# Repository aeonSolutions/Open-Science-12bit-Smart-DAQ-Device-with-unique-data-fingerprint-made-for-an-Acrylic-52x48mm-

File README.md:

<br>

[PCB-Prototyping-Catalogue](https://github.com/aeonSolutions/PCB-Prototyping-Catalogue)  >>  [Open Scientific Research](https://github.com/aeonSolutions/Open-Scientific-Research)  >>  12bit-Smart-DAQ-unique-data-fingerprint-made-for-an-Acrylic-52x48mm

# 12bit Smart DAQ Device with unique data fingerprint and a 1.69" TFT LCD made for an Acrylic 52x48mm  Enclosure

This is the repository for the 12bit Smart DAQ Device with unique data fingerprint able to do experimental data upload to any data repository. For detailed information head to the main project Wiki [here](https://github.com/aeonSolutions/openScience-Smart-DAQ-to-Upload-Live-Experimental-Data-to-a-Data-Repository/wiki). Thank you.

<br>

### 12bit Smart DAQ  Hardware Specifications
The hardware specifications for the 12bit PCB with dimensions of 52x46mm are the following:

- QFN 56 Dual Xtensa LX7 Core Processors running up to 240MHz
  -	RISC V ultra-low power co-processor
  - 512Kb RAM (PSRAM max 1 Gb);
  - 16Mb SOIC 8 NOR SPI Flash Memory (max 1Gb);
  - 2.4GHz ISM wireless connectivity;
  - Up to 118 12bit ADC Multiplexed DAQ channels;

<br>

- Onboard Storage:
  - 2x SPI Flash WSON-8 Chips for local storage upwards of 4Gbytes. 

<br>

- Authentication & Security:
  - SOIC-8 ATSHA204A SHA-256 high-security hardware authentication IC for secure and unique experimental data exchange

<br>

- Power management
  - DFN-6 AUR9718/ST1S09 high efficiency step-down 3.3V 1.5A DC converter;
  - CN3065 4.2V Lipo Battery Management System
  - USB-C connection for 5.0V 1.0A power supply from any power charger found on smartphones or tablets.
  - JST SH 2 pin 1.0mm for specific power supply applications (3.3V to 5.0V 1.0A DC)    

<br>

- Connectivity
  - 2.4GHz WIFI
  - Bluetooth & BLE
  - USB-C serial communication
  - JTAG debugger connector
  - Serial UART connector
  
<br>

- Onboard sensors:
  - DFN-8 AHT20; temperature sensor with a precision of 0.1 C;
  - DFN-8 AHT20 humidity sensor;
  - LGA-14 LSM6DS3 a 6-axis accelerometer and gyroscope;
  - TEMT6000 Luminosity Sensor;
  - SOT 23-3 reference voltage sensor;

<br>

- External connectivity for up to 118 sensors 12 to 16bit with onboard voltage reference analyzer with temperature compensation and automatic ADC calibration:
  -  1x I2C pin terminal connector (4 pin)
  -  1x ADC 12 to 16bit (with oversampling & digitization) digital terminal connector (3 pin)
  -  1x ADC Ohmmeter connection with 12 to 16bit (with oversampling & digitization) with manual scale selection via dip switch
 
<br>

- Display
  - 1.69" TFT LCD Display with a resolution of 320x280 px 

<br>

- Enclosure

This particular smart DAQ was designed to fit a well-known ABS enclosure commercially available on the internet. For instance [here](https://s.click.aliexpress.com/e/_DCKIAm1) on AliExpress. 

<br>

<br>

<p align="center">

</p>

<br>

###  Status

Fully tested and working

 **Known PCB bugs [April 04-2023 pcb revision] :**
 
UART SH connector GND pin requires connection to GND on the PCB (easy fix. as it is exactly next to the GND pin). This only affects the onboard firmware upload UART port (the OEM firmware available here is able to do OTA updates using WIFI) .   

<br>

<p align="center">     

</p>

<br>

## What one additionally needs
- [USB to UART/USB TTL firmware burner for 5V and 3.3V MCUs ](https://github.com/aeonSolutions/PCB-Prototyping-Catalogue/blob/main/DIY-Maker/README.md) 

<br />
<br />

## Dataverse API C library

In paralell is being written a C library to expedite API integration on smart DAQ devices or elsewhere. Follow the link to its repository:

https://github.com/aeonSolutions/OpenScience-Dataverse-API-C-library

<p align="center">
  
</p>

<br>

**Dataverse API in another coding language**

Goto dataverse.org for another coding language that best suits your coding style and needs. Currently there are client libraries for Python, Javascript, R, Java, and Julia that can be used to develop against Dataverse Software APIs

https://guides.dataverse.org/en/5.12/api/client-libraries.html

<br>
<br>

-----------------------------------------------------------------------------------

**Get a Notification on every PCB update**

|  | You can fill in your [email here (Google form)](https://docs.google.com/forms/d/e/1FAIpQLScErMgQYRdA-umvCjvTPPrCO7Lg1QYowTxb7vfa8cTfrcPEAA/viewform?usp=pp_url) and I'll send a reminder when a new PCB prototype is made available here or a new revision for an existing PCB. Stay tuned! |
|-------------|------|

<br />

**Be supportive of my dedication and work towards open hardware and buy me a cup of coffee. Links below. Above and on the side**

<br />
<br />

## Q&A WhatsApp/Telegram Groups
|  | Subscribe to the WhatsApp or Telegram channel to get latest information about any of this KiCad projects and get help. Or simply like this kind of projects and want to stay updated with the latest research ideas and prototypes during the day and week.   |
|-------------|------|

<br />
<br />

## Usefull Utilities 
|  | One can find here usefull utilities to use when designing and prototyping pcb electronics. For instance a simple excel spreadsheet with resistance divider finder compatible with all sold on [aliexpress](https://www.aliexpress.com/item/1005002792418456.html?spm=a2g0o.cart.0.0.22e538dayDM1YR&mp=1). Click on the Excel logo to the left to get them! |
|-------------|------|

<br />
<br />

## Author

You can get in touch with me on my LinkedIn Profile:

*Miguel Tomas* : 

You can also follow my GitHub Profile to stay updated about my latest projects: 

<br>

### Be supportive of my dedication and work towards open innovation & technology solutions and buy me a cup of coffee
The PCB Design Files I provide here for anyone to use are free. If you like this Smart Device or use it, please consider buying me a cup of coffee, a slice of pizza, or a book to help me study, eat and think new PCB design files.

<p align+"left">

<br>

</p>

<br />

### Make a donation on Paypal
Make a donation on PayPal and get a TAX refund*.

<br>

### Support all these open hardware projects and become a Patreon  
Liked any of my PCB KiCad Designs? Help and Support my open work to all by becoming an LDAD Patreon.
In return, I will give a free PCB design in KiCad to all Patreon supporters. To learn more go to patreon.com. Link below.

<br />
<br />

______________________________________________________________________________________________________________________________
### License
2023 Creative Commons Attribution-NonCommercial-ShareAlike 4.0 International

https://creativecommons.org/licenses/by-nc-sa/4.0/

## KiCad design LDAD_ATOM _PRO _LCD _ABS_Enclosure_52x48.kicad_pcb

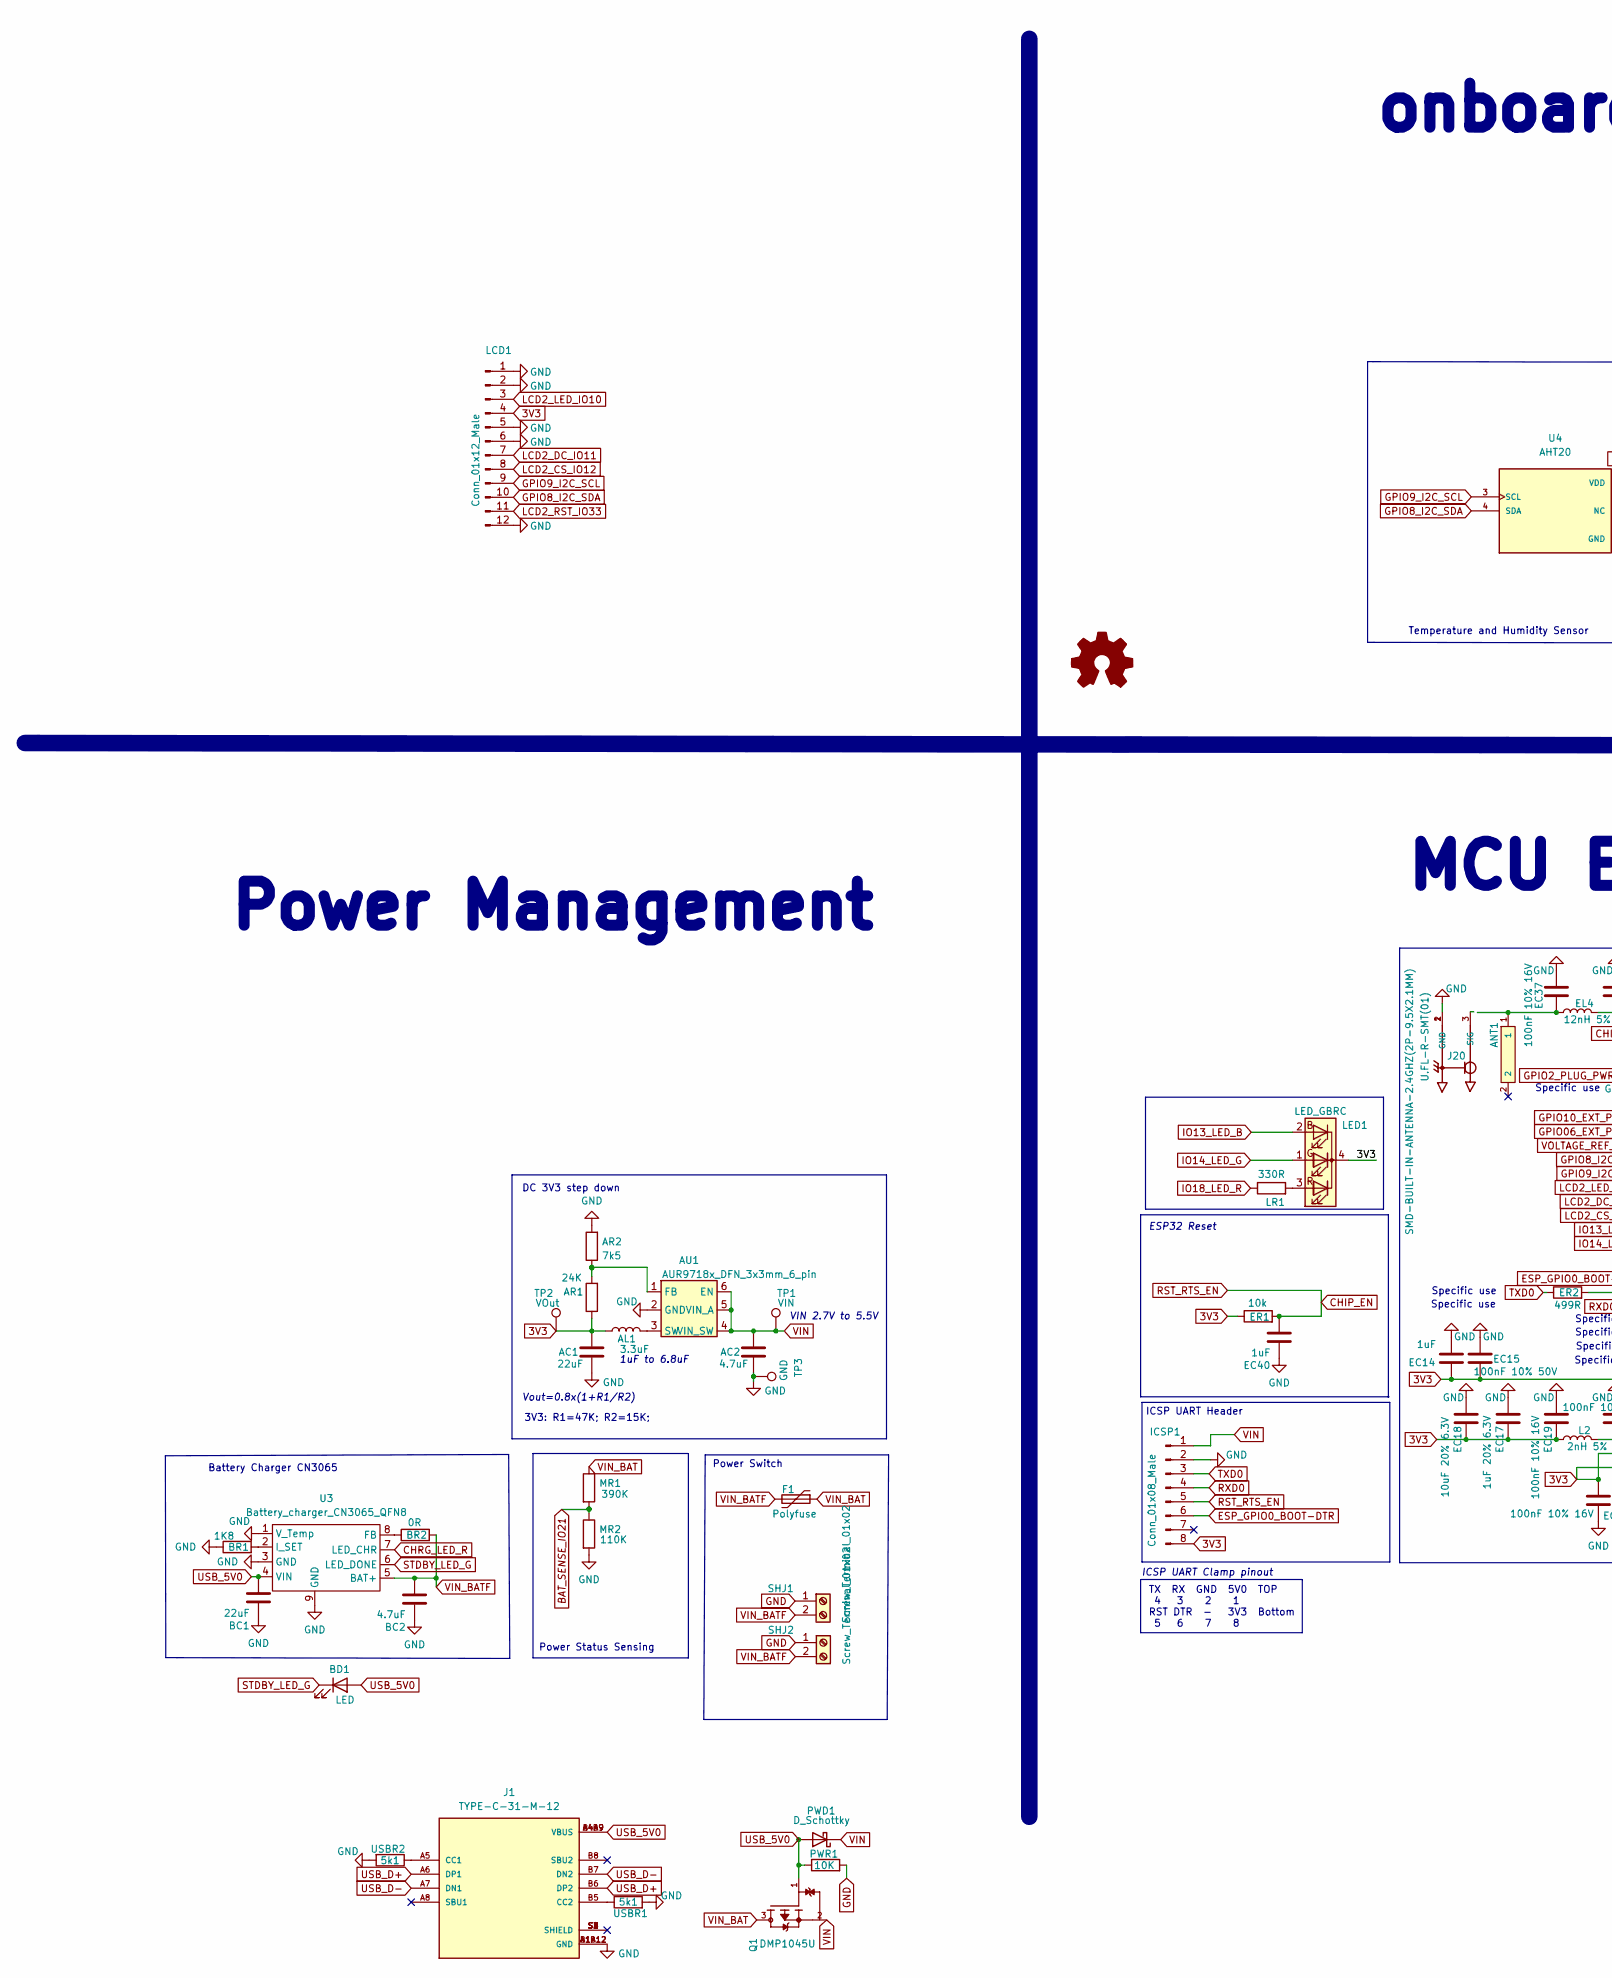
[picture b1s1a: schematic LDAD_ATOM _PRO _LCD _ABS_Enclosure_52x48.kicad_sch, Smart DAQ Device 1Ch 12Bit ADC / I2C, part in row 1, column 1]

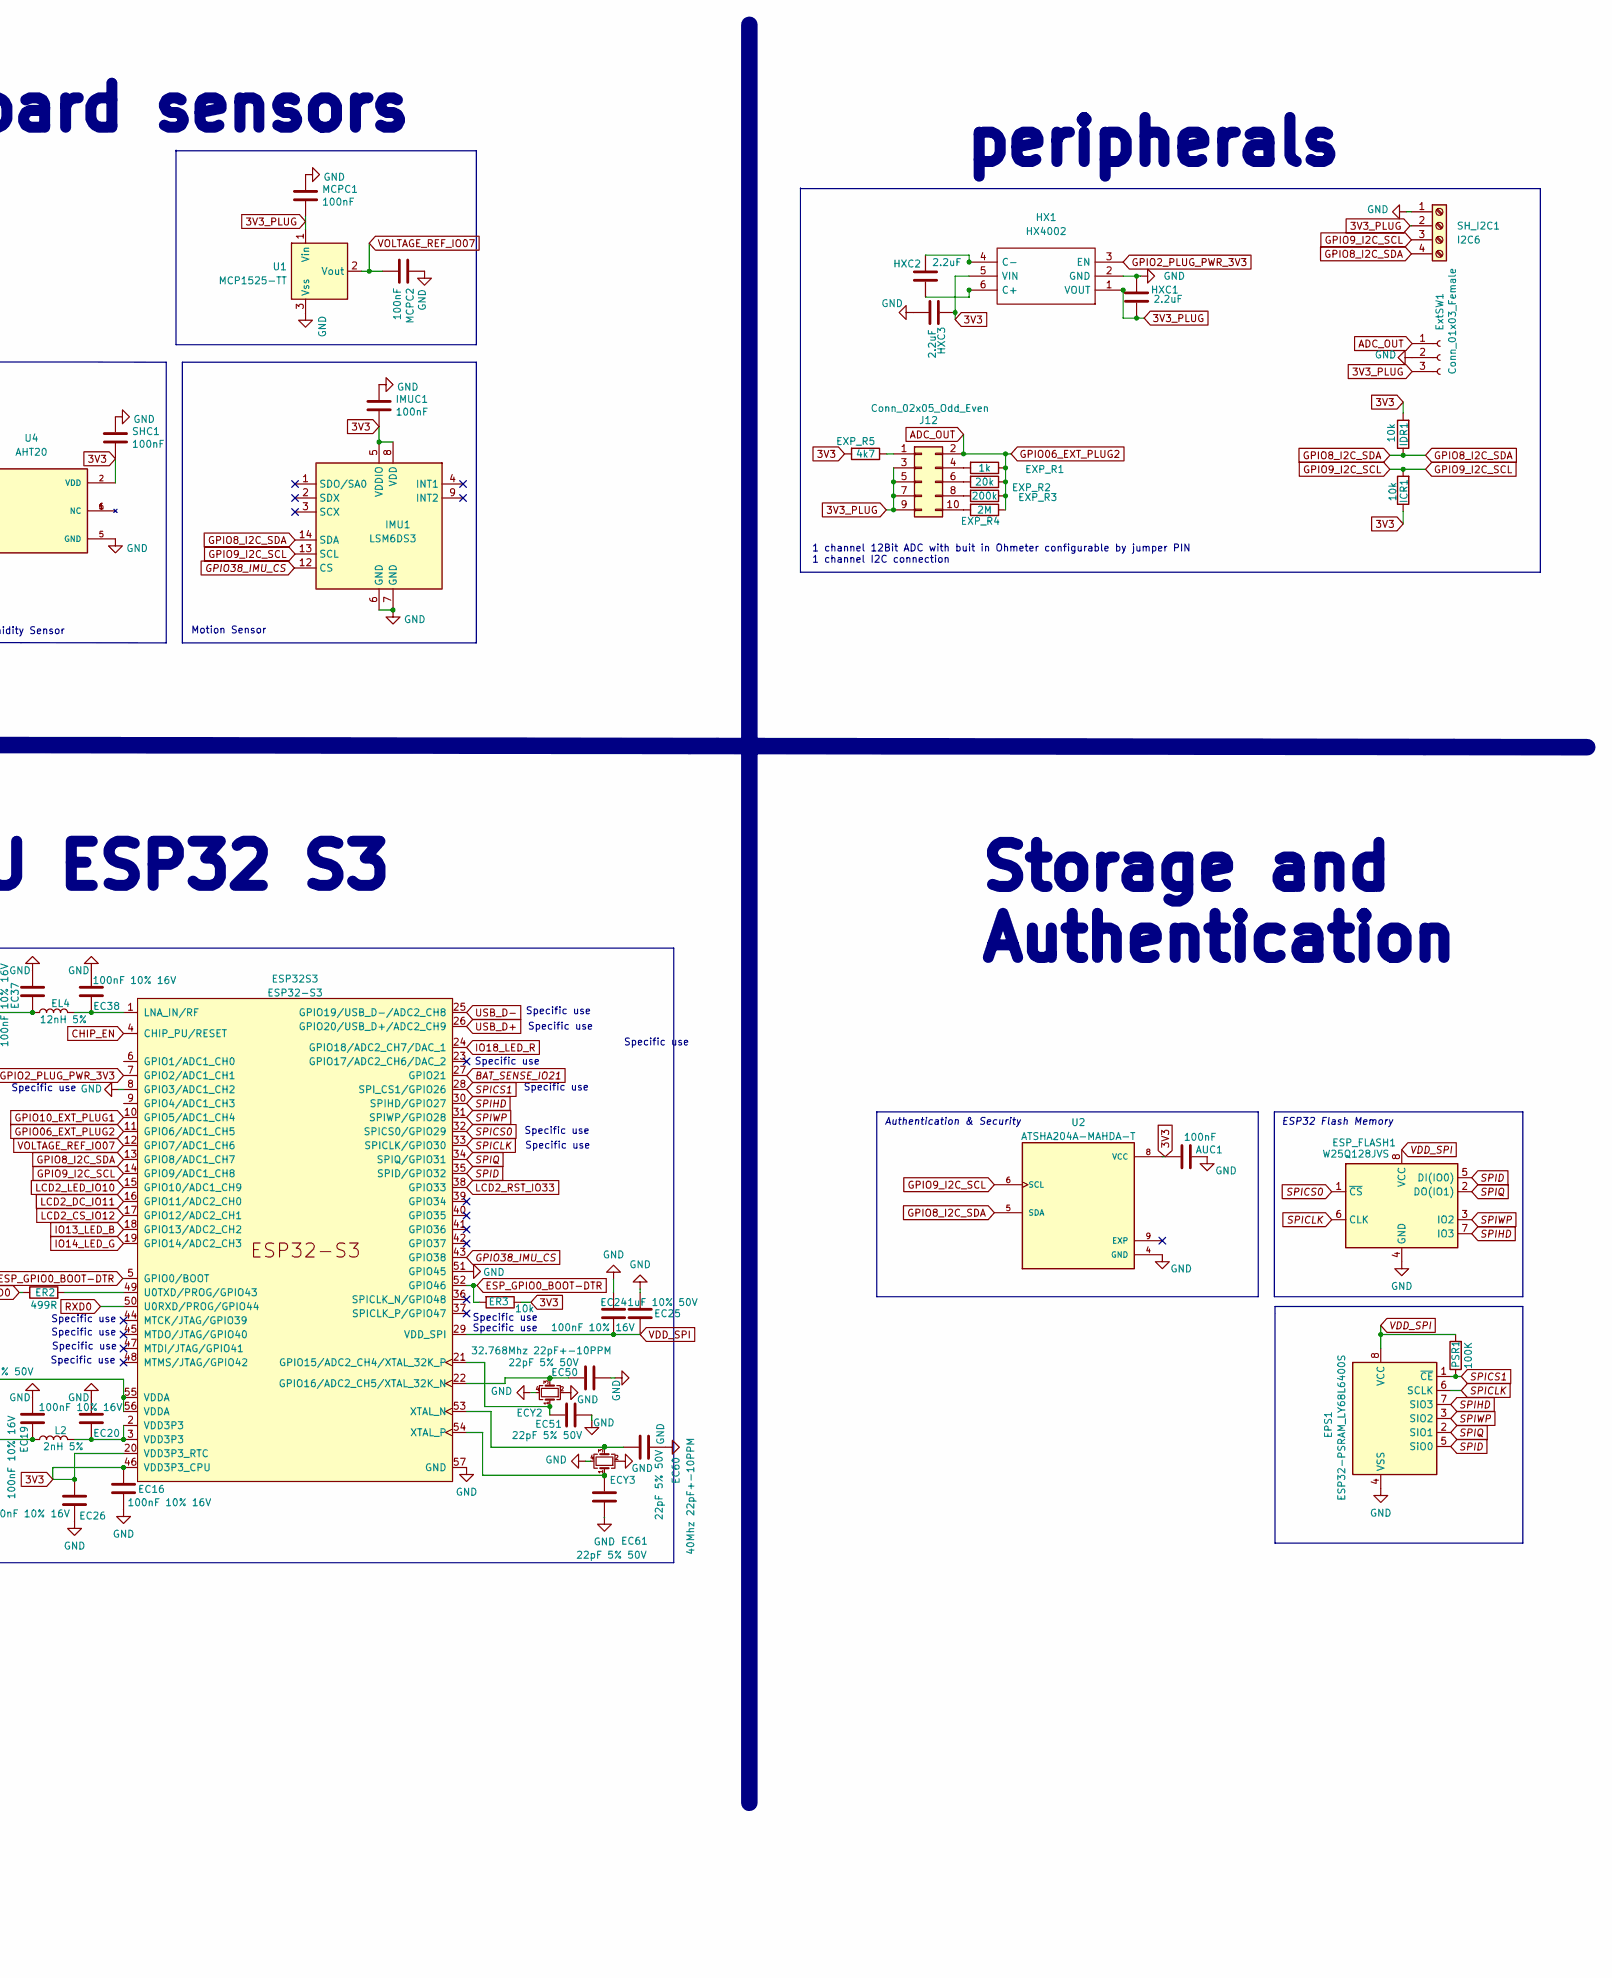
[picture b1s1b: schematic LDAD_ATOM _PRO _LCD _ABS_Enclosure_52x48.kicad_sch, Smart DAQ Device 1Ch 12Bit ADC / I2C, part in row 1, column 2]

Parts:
AC1: 22uF; C_0805_2012Metric_Pad1.18x1.45mm_HandSolder
AC2: 4.7uF; C_0805_2012Metric_Pad1.18x1.45mm_HandSolder
AL1: 3.3uF; L_1210_3225Metric
ANT1: SMD-BUILT-IN-ANTENNA-2.4GHZ(2P-9.5X2.1MM); AN9520_ANT2-SMD-9.5X2.1X1.0MM
AR1: 24K; R_0805_2012Metric_Pad1.20x1.40mm_HandSolder
AR2: 7k5; R_0805_2012Metric_Pad1.20x1.40mm_HandSolder
AU1: AUR9718x_DFN_3x3mm_6_pin; AUR9718 3x3mm 6 pin
AUC1: 100nF; C_0603_1608Metric
BC1: 22uF; C_0805_2012Metric
BC2: 4.7uF; C_0805_2012Metric
BD1: LED; LED_0805_2012Metric
BR1: 1K8; R_0603_1608Metric
BR2: 0R; R_0603_1608Metric
EC14: 1uF; C_0805_2012Metric
EC15: 100nF 10% 50V; C_0603_1608Metric
EC16, EC19, EC20, EC24, EC26, EC37, EC38: 100nF 10% 16V; C_0603_1608Metric
EC17: 1uF 20% 6.3V; C_0603_1608Metric
EC18: 10uF 20% 6.3V; C_0805_2012Metric
EC25: 1uF 10% 50V; C_0603_1608Metric
EC40: 1uF; C_0603_1608Metric
EC50, EC51, EC60, EC61: 22pF 5% 50V; C_0603_1608Metric
ECY2: 32.768Mhz 22pF+-10PPM; Crystal_SMD_EuroQuartz_MT-4Pin_3.2x2.5mm
ECY3: 40Mhz 22pF+-10PPM; Crystal_SMD_EuroQuartz_MT-4Pin_3.2x2.5mm
EL4: 12nH 5%; L_0805_2012Metric
EPS1: ESP32-PSRAM_LY68L6400S; SOIC-8_3.9x4.9mm_P1.27mm
ER1, ER3: 10k; R_0603_1608Metric
ER2: 499R; R_0603_1608Metric
ESP32S3: ESP32-S3; QFN-56-1EP_7x7mm_P0.4mm_EP5.6x5.6mm
ESP_FLASH1: W25Q128JVS; Flash SPI SON127P800X600X80-9N
EXP_R1: 1k; R_0603_1608Metric
EXP_R2: 20k; R_0603_1608Metric
EXP_R3: 200k; R_0603_1608Metric
EXP_R4: 2M; R_0603_1608Metric
EXP_R5: 4k7; R_0603_1608Metric
ExtSW1: Conn_01x03_Female; JST_SH_SM03B-SRSS-TB_1x03-1MP_P1.00mm_Horizontal
F1: Polyfuse; Fuse_1206_3216Metric_Pad1.42x1.75mm_HandSolder
HX1: HX4002; HX4002 SOT95 P280X125-6N; Manufacturer_Part_Number HX4002
HXC1, HXC2, HXC3: 2.2uF; C_0603_1608Metric
ICR1: 10k; R_0603_1608Metric
ICSP1: Conn_01x08_Male; SOIC_clipProgSmall
IDR1: 10k; R_0603_1608Metric
IMU1: LSM6DS3; LSM6DS3 PQFN50P300X250X86-14N
IMUC1: 100nF; C_0603_1608Metric
J1: TYPE-C-31-M-12; USB C HRO_TYPE-C-31-M-12; PARTREV A
J12: Conn_02x05_Odd_Even; Dip Switch 5 pin 1.27mm SW_DS05-127-2-06BK-SMT-TR
J20: U.FL-R-SMT(01); HRS_U.FL-R-SMT(01)
L2: 2nH 5%; L_0805_2012Metric
LCD1: Conn_01x12_Male; 1.69 LCD TFT IPS 12pin
LED1: LED_GBRC; LED_1206_3210_RGB_Metric
LR1: 330R; R_0603_1608Metric
MCPC1, MCPC2: 100nF; C_0603_1608Metric
MR1: 390K; R_0805_2012Metric
MR2: 110K; R_0805_2012Metric
PSR1: 100K; R_0603_1608Metric
PWD1: D_Schottky; D_1206_3216Metric
PWR1: 10K; R_0805_2012Metric
Q1: DMP1045U; SOT-23; PARTREV 7 - 2
SHC1: 100nF; C_0603_1608Metric
SHJ1, SHJ2: Screw_Terminal_01x02; JST_SH_SM02B-SRSS-TB_1x02-1MP_P1.00mm_Horizontal
SH_I2C1: I2C6; JST_SH_SM04B-SRSS-TB_1x04-1MP_P1.00mm_Horizontal
TP1: VIN; TestPoint_Pad_D1.0mm
TP2: VOut; TestPoint_Pad_D1.0mm
TP3: GND; TestPoint_Pad_D1.0mm
U1: MCP1525-TT; SOT-23
U2: ATSHA204A-MAHDA-T; ATSHA204A Auth SOIC8; PART_REV A
U3: Battery_charger_CN3065_QFN8; QFN8 3.1x2.9mm QFNn-8 3x3 SON80P400X400X100-9N
U4: AHT20; AHT20 - PSON100P300X300X110-6N; PARTREV V1.0
USBR1, USBR2: 5k1; R_0603_1608Metric

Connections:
3V3: AC1.1, AL1.1, AR1.1, AUC1.2, EC14.2, EC15.2, EC16.1, EC17.1, EC18.1, EC19.1, EC26.1, ER1.1, ER3.1, ESP32S3.20 (VDD3P3_RTC), ESP32S3.46 (VDD3P3_CPU), ESP32S3.55 (VDDA), ESP32S3.56 (VDDA), EXP_R5.2, HX1.5 (VIN), HXC3.2, ICR1.1, ICSP1.8, IDR1.2, IMU1.5 (VDDIO), IMU1.8 (VDD), IMUC1.2, L2.1, LCD1.4, LED1.4 (K), SHC1.2, TP2.1, U2.8 (VCC), U4.2 (VDD)
3V3_PLUG: ExtSW1.3, HX1.1 (VOUT), HXC1.1, J12.3, J12.5, J12.7, J12.9, MCPC1.2, SH_I2C1.2, U1.1 (Vin)
ADC_OUT: ESP32S3.11 (GPIO6/ADC1_CH5), EXP_R1.1, EXP_R2.1, EXP_R3.1, EXP_R4.1, ExtSW1.1, J12.2
BAT_SENSE_IO21: ESP32S3.27 (GPIO21), MR1.2, MR2.1
CHIP_EN: EC40.2, ER1.2, ESP32S3.4 (CHIP_PU/RESET), ICSP1.5
CHRG_LED_R: U3.7 (LED_CHR)
ESP_GPIO0_BOOT-DTR: ER3.2, ESP32S3.5 (GPIO0/BOOT), ESP32S3.52 (GPIO46), ICSP1.6
GND: AC1.2, AC2.2, AR2.2, AU1.2 (GND), AUC1.1, BC1.1, BC2.1, BR1.1, EC14.1, EC15.1, EC16.2, EC17.2, EC18.2, EC19.2, EC20.2, EC24.2, EC25.2, EC26.2, EC37.2, EC38.2, EC40.1, EC50.2, EC51.2, EC60.2, EC61.2, ECY2.2, ECY2.4, ECY3.2, ECY3.4, EPS1.4 (VSS), ESP32S3.8 (GPIO3/ADC1_CH2), ESP32S3.51 (GPIO45), ESP32S3.57 (GND), ESP_FLASH1.4 (GND), ExtSW1.2, HX1.2 (GND), HXC1.2, HXC3.1, ICSP1.2, IMU1.6 (GND), IMU1.7 (GND), IMUC1.1, J1.A1B12 (GND), J1.B1A12 (GND), J20.1 (GND), J20.2 (GND), LCD1.1, LCD1.2, LCD1.5, LCD1.6, LCD1.12, MCPC1.1, MCPC2.1, MR2.2, PWR1.2, SHC1.1, SHJ1.1, SHJ2.1, SH_I2C1.1, TP3.1, U1.3 (Vss), U2.4 (GND), U3.1 (V_Temp), U3.3 (GND), U3.9 (GND), U4.5 (GND), USBR1.2, USBR2.2
GPIO2_PLUG_PWR_3V3: ESP32S3.7 (GPIO2/ADC1_CH1), HX1.3 (EN)
GPIO8_I2C_SDA: ESP32S3.13 (GPIO8/ADC1_CH7), IDR1.1, IMU1.14 (SDA), LCD1.10, SH_I2C1.4, U2.5 (SDA), U4.4 (SDA)
GPIO9_I2C_SCL: ESP32S3.14 (GPIO9/ADC1_CH8), ICR1.2, IMU1.13 (SCL), LCD1.9, SH_I2C1.3, U2.6 (SCL), U4.3 (SCL)
GPIO10_EXT_PLUG1: ESP32S3.10 (GPIO5/ADC1_CH4)
GPIO38_IMU_CS: ESP32S3.43 (GPIO38), IMU1.12 (CS)
IO13_LED_B: ESP32S3.18 (GPIO13/ADC2_CH2), LED1.2 (BA)
IO14_LED_G: ESP32S3.19 (GPIO14/ADC2_CH3), LED1.1 (GA)
IO18_LED_R: ESP32S3.24 (GPIO18/ADC2_CH7/DAC_1), LR1.1
LCD2_CS_IO12: ESP32S3.17 (GPIO12/ADC2_CH1), LCD1.8
LCD2_DC_IO11: ESP32S3.16 (GPIO11/ADC2_CH0), LCD1.7
LCD2_LED_IO10: ESP32S3.15 (GPIO10/ADC1_CH9), LCD1.3
LCD2_RST_IO33: ESP32S3.38 (GPIO33), LCD1.11
unnamed: AL1.2, AU1.3 (SW)
unnamed: ANT1.1, EC37.1, EL4.1
unnamed: AR1.2, AR2.1, AU1.1 (FB)
unnamed: BR1.2, U3.2 (I_SET)
unnamed: BR2.1, U3.8 (FB)
unnamed: EC20.1, ESP32S3.2 (VDD3P3), ESP32S3.3 (VDD3P3), L2.2
unnamed: EC38.1, EL4.2, ESP32S3.1 (LNA_IN/RF)
unnamed: EC50.1, ECY2.3, ESP32S3.22 (GPIO16/ADC2_CH5/XTAL_32K_N)
unnamed: EC51.1, ECY2.1, ESP32S3.21 (GPIO15/ADC2_CH4/XTAL_32K_P)
unnamed: EC60.1, ECY3.3, ESP32S3.53 (XTAL_N)
unnamed: EC61.1, ECY3.1, ESP32S3.54 (XTAL_P)
unnamed: ER2.2, ESP32S3.49 (U0TXD/PROG/GPIO43)
unnamed: EXP_R1.2, J12.4
unnamed: EXP_R2.2, J12.6
unnamed: EXP_R3.2, J12.8
unnamed: EXP_R4.2, J12.10
unnamed: EXP_R5.1, J12.1
unnamed: HX1.4 (C-), HXC2.2
unnamed: HX1.6 (C+), HXC2.1
unnamed: J1.A5 (CC1), USBR2.1
unnamed: J1.B5 (CC2), USBR1.1
unnamed: LED1.3 (RA), LR1.2
RXD0: ESP32S3.50 (U0RXD/PROG/GPIO44), ICSP1.4
SPICLK: EPS1.6 (SCLK), ESP32S3.33 (SPICLK/GPIO30), ESP_FLASH1.6 (CLK)
SPICS0: ESP32S3.32 (SPICS0/GPIO29), ESP_FLASH1.1 (~CS)
SPICS1: EPS1.1 (~CE), ESP32S3.28 (SPI_CS1/GPIO26), PSR1.1
SPID: EPS1.5 (SiO0), ESP32S3.35 (SPID/GPIO32), ESP_FLASH1.5 (DI(IO0))
SPIHD: EPS1.7 (SIO3), ESP32S3.30 (SPIHD/GPIO27), ESP_FLASH1.7 (IO3)
SPIQ: EPS1.2 (SIO1), ESP32S3.34 (SPIQ/GPIO31), ESP_FLASH1.2 (DO(IO1))
SPIWP: EPS1.3 (SIO2), ESP32S3.31 (SPIWP/GPIO28), ESP_FLASH1.3 (IO2)
STDBY_LED_G: BD1.1 (K), U3.6 (LED_DONE)
TXD0: ER2.1, ICSP1.3
USB_5V0: BC1.2, BD1.2 (A), J1.A4B9 (VBUS), J1.B4A9 (VBUS), PWD1.2 (A), PWR1.1, Q1.1, U3.4 (VIN)
USB_D+: ESP32S3.26 (GPIO20/USB_D+/ADC2_CH9), J1.A6 (DP1), J1.B6 (DP2)
USB_D-: ESP32S3.25 (GPIO19/USB_D-/ADC2_CH8), J1.A7 (DN1), J1.B7 (DN2)
VDD_SPI: EC24.1, EC25.1, EPS1.8 (VCC), ESP32S3.29 (VDD_SPI), ESP_FLASH1.8 (VCC), PSR1.2
VIN: AC2.1, AU1.4 (VIN_SW), AU1.5 (VIN_A), AU1.6 (EN), ICSP1.1, PWD1.1 (K), Q1.2, TP1.1
VIN_BAT: F1.1, MR1.1, Q1.3
VIN_BATF: BC2.2, BR2.2, F1.2, SHJ1.2, SHJ2.2, U3.5 (BAT+)
VOLTAGE_REF_IO07: ESP32S3.12 (GPIO7/ADC1_CH6), MCPC2.2, U1.2 (Vout)

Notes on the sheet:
Specific use
3V3: R1=47K; R2=15K;
ICSP UART Header
peripherals
Vout=0.8x(1+R1/R2)
ESP32 Flash Memory
DC 3V3 step down
ESP32 Reset
Temperature and Humidity Sensor
1uF to 6.8uF
Motion Sensor
1 channel 12Bit ADC with buit in Ohmeter configurable by jumper PIN 1 channel I2C connection
onboard sensors
ICSP UART Clamp pinout
Storage and Authentication
Battery Charger CN3065
Power Management
Authentication & Security
VIN 2.7V to 5.5V
Power Switch
MCU ESP32 S3
TX RX GND 5V0 TOP 4 3 2 1 RST DTR - 3V3 Bottom 5 6 7 8
Power Status Sensing

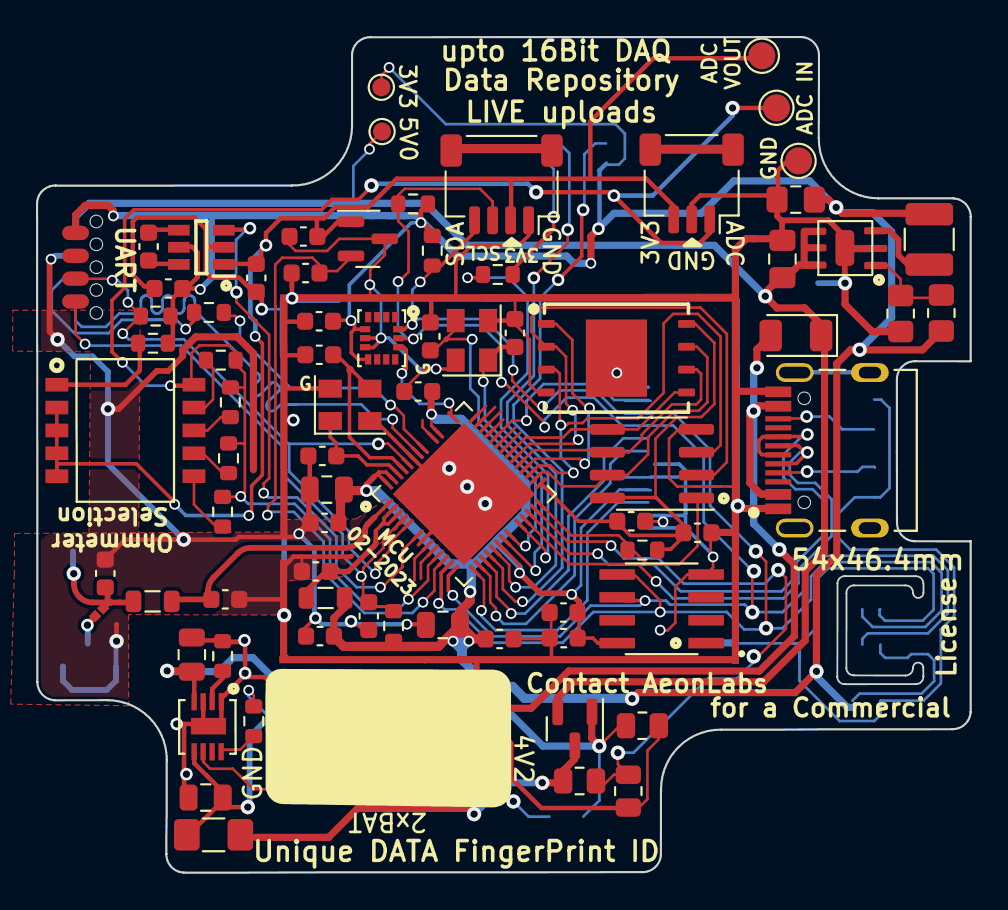
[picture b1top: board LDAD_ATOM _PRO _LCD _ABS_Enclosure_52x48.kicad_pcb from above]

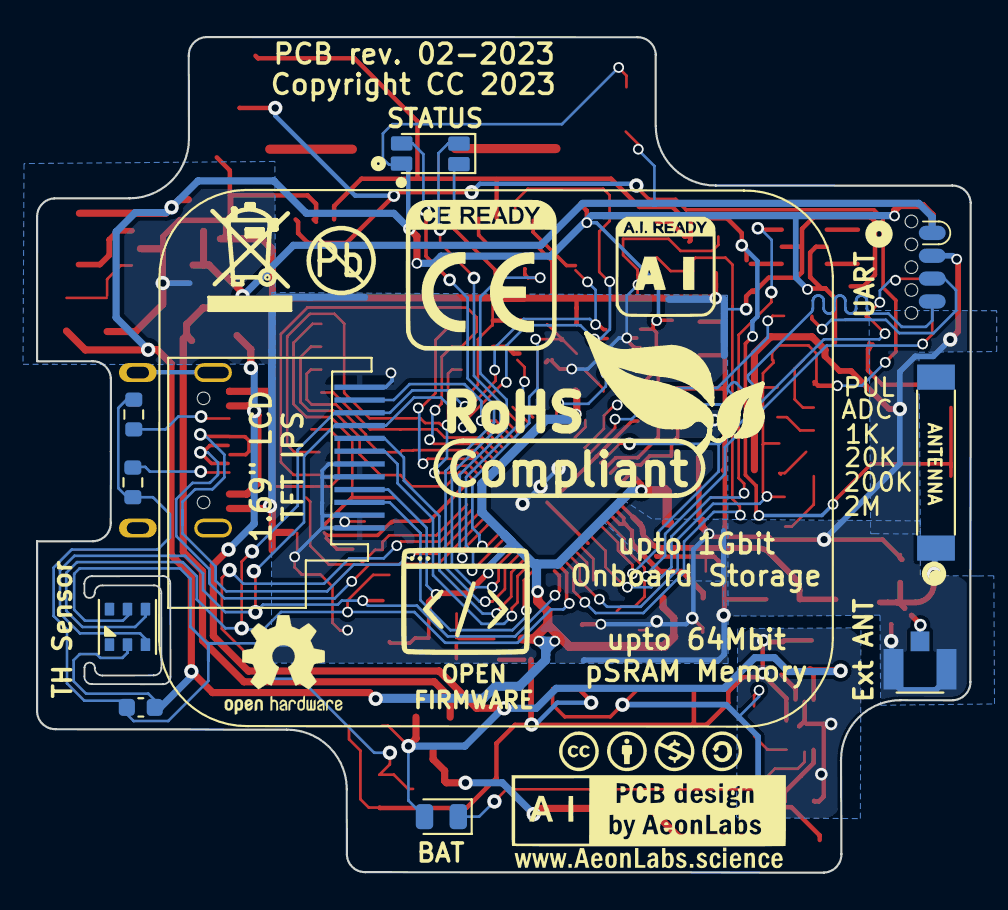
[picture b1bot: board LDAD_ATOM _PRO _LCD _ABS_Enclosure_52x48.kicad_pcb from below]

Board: 2 copper layers, 51.9 x 46.4 mm, 85 parts (13 on the bottom side), 58 nets.

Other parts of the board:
Sign-PbFree: LOGO_PBFREE
Sign-RecycleBin: LOGO_RECYCLEBIN_1
Sign-RoHS: LOGO_ROHS_1

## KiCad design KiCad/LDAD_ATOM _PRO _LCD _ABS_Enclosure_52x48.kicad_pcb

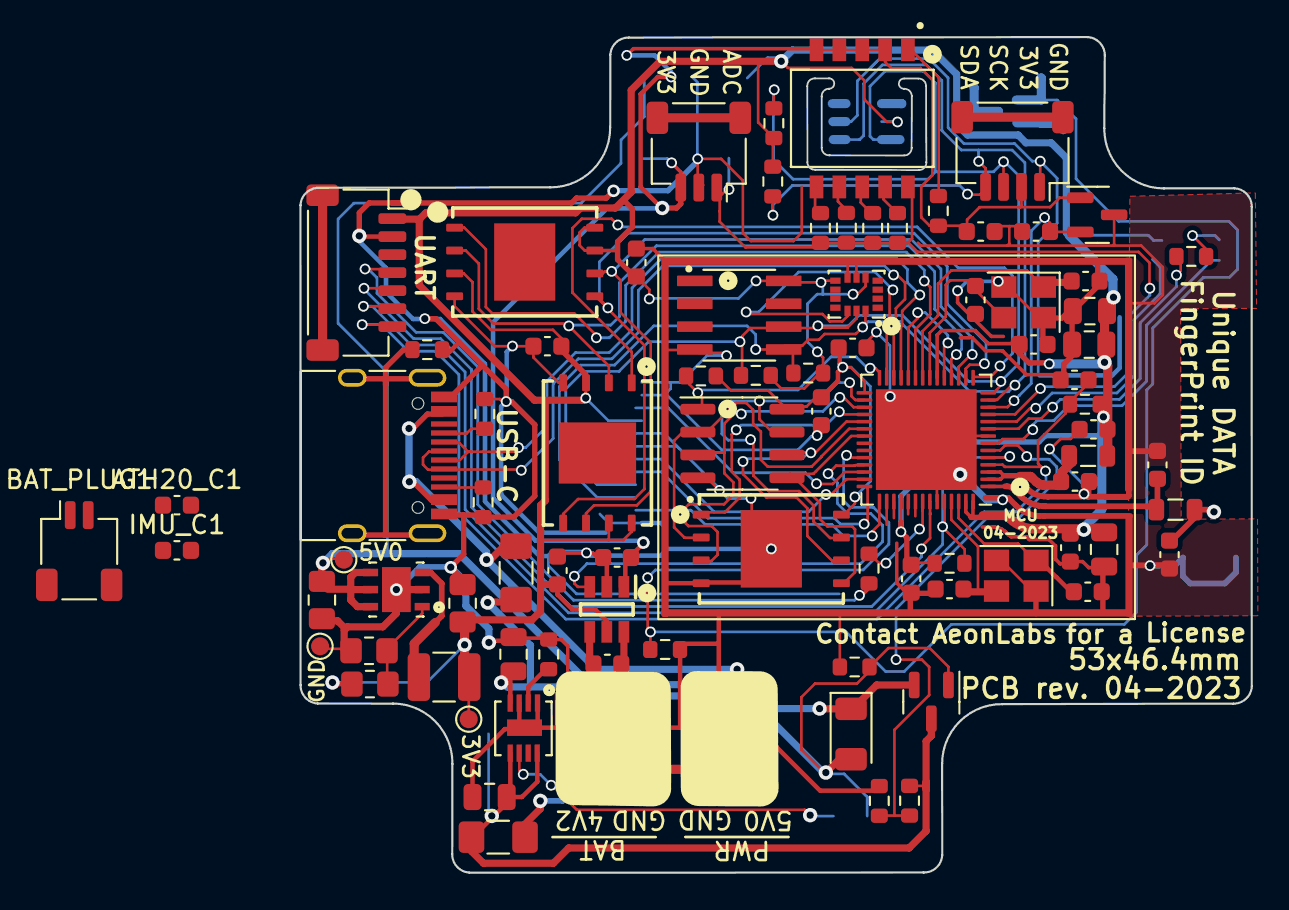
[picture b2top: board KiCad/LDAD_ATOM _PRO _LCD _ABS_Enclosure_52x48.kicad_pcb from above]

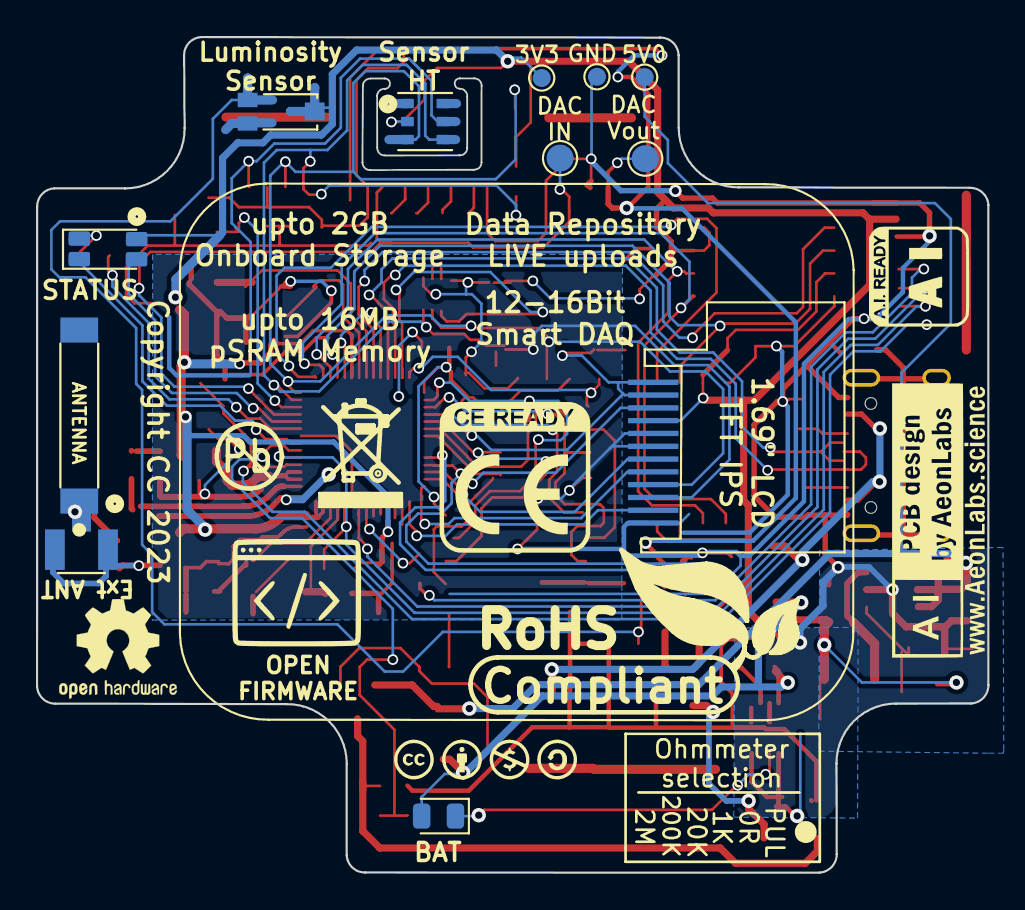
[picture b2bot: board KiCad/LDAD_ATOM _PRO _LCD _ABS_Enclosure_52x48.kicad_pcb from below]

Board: 2 copper layers, 52.9 x 46.4 mm, 99 parts (13 on the bottom side), 66 nets.

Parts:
ATH20_C1: 100nF; C_0603_1608Metric
ATSHA_C1: 100nF; C_0603_1608Metric
AUR1: AUR9718x_DFN_3x3mm_6_pin; AUR9718 ST1S09 SON95P300X300X100-7N
AUR_C1: 22uF; C_0805_2012Metric_Pad1.18x1.45mm_HandSolder
AUR_C2: 4.7uF; C_0805_2012Metric_Pad1.18x1.45mm_HandSolder
AUR_R1: 24K; R_0805_2012Metric_Pad1.20x1.40mm_HandSolder
AUR_R2: 7k5; R_0805_2012Metric_Pad1.20x1.40mm_HandSolder
AUR_l1: 3.3uF; L_1210_3225Metric
BAT_FUSE1: Polyfuse; Fuse_1206_3216Metric_Pad1.42x1.75mm_HandSolder
BAT_PLUG1: Screw_Terminal_01x02; JST_SH_SM02B-SRSS-TB_1x02-1MP_P1.00mm_Horizontal
BAT_SENSE_R1, BAT_SENSE_R2: 100k; R_0603_1608Metric
CN3065_C2: 4.7uF; C_0805_2012Metric
CN3065_R1: 1K8; R_0603_1608Metric
CN3065_STDBY_LED1: LED; LED_0805_2012Metric
CN3965_C1: 22uF; C_0805_2012Metric
DIPSW1: Conn_02x05_Odd_Even; Dip Switch 5pin 1mm SW_DS05-127-2-06BK-SMT-TR
DIP_R1: 4k7; R_0603_1608Metric
DIP_R2: 1k; R_0603_1608Metric
DIP_R3: 20k; R_0603_1608Metric
DIP_R4: 200k; R_0603_1608Metric
DIP_R5: 2M; R_0603_1608Metric
DMP1045U_1: DMP1045U; SOT-23
DMP1045_R1: 10K; R_0603_1608Metric
DMP1045_SCHOT1: D_Schottky; D_1206_3216Metric
EPS1: ESP32-PSRAM_LY68L6400S; SOIC-8_3.9x4.9mm_P1.27mm
ESP32S1: ESP32-S3; QFN-56-1EP_7x7mm_P0.4mm_EP5.6x5.6mm
ESP32_SHIELD1: RFShield_OnePiece; ESP32-S3 GND Shield
ESP_FLASH1, ESP_FLASH2, ESP_FLASH3: W25Q128JVS; WSON8 FLASH SPI SON127P800X600X80-9N
E_DTR_R1: 10k; R_0603_1608Metric
E_LNA_ANT1: AN9520; 2.4ghZ WIFI ANTENNA AN9520_ANT2-SMD-9.5X2.1X1.0MM
E_LNA_ANT2: U.FL-R-SMT(01); RF Antenna IPEX SMD PCB HRS_U.FL-R-SMT(01)
E_LNA_C1, E_LNA_C2: 2.7pF; C_0603_1608Metric
E_LNA_l1: 1.8nH 5%; L_0805_2012Metric
E_RTS_C1: 100nF; C_0603_1608Metric
E_RTS_R1: 10k; R_0603_1608Metric
E_SPI_C1: 1uF 10% 50V; C_0603_1608Metric
E_SPI_C2: 100nF 10% 16V; C_0603_1608Metric
E_UART_TX_1: 499R; R_0603_1608Metric
E_VDDA_C1: 100nF; C_0603_1608Metric
E_VDDA_C2: 1uF 10% 50V; C_0805_2012Metric
E_VDD_3_C1, E_VDD_3_C2: 10uF 20% 6.3V; C_0805_2012Metric
E_VDD_3_C3, E_VDD_3_C4: 100nF 10% 16V; C_0603_1608Metric
E_VDD_CPU_C1: 100nF 10% 16V; C_0603_1608Metric
E_VDD_L1: 12nH 5%; L_0805_2012Metric
E_VDD_RTC_C1: 100nF 10% 16V; C_0603_1608Metric
E_XTAL32_1: 32.768Mhz 22pF+-10PPM; Crystal_SMD_3225-4Pin_3.2x2.5mm
E_XTAL32_C1, E_XTAL32_C2, E_XTAL40_C1, E_XTAL40_C2: 22pF 5% 50V; C_0603_1608Metric
E_XTAL40_1: 40Mhz 22pF+-10PPM; Crystal_SMD_3225-4Pin_3.2x2.5mm
ExtSW1: Conn_01x03_Female; JST_SH_SM03B-SRSS-TB_1x03-1MP_P1.00mm_Horizontal
ExtSWBAT_PLUG2: Conn_01x03_Female; JST_SH_SM03B-SRSS-TB_1x03-1MP_P1.00mm_Horizontal
HX1: HX4002; HX4002 SOT95 P280X125-6N
HX_C1, HX_C2, HX_C3: 2.2uF; C_0603_1608Metric
I2C_PLUG1: I2C6; JST_SH_SM04B-SRSS-TB_1x04-1MP_P1.00mm_Horizontal
I2C_SCL_R1, I2C_SDA_R1: 10k; R_0603_1608Metric
IMR1, IMR2: 10K; R_0603_1608Metric
IMU1: LSM6DS3; LSM6DS3 Motion Sensor PQFN50P300X250X86-14N
IMU_C1: 100nF; C_0603_1608Metric
J1: TYPE-C-31-M-12; USB_C_Receptacle_HRO_TYPE-C-31-M-12
JICSP1: Conn_01x07_Socket; JST_SH_SM07B-SRSS-TB_1x07-1MP_P1.00mm_Horizontal
LCD1: Conn_01x12_Male; 1,69 inch LCD IPS TFT
LED1: LED_GBRC; LED_1206_3210_RGB_Metric
LR1: 330R; R_0603_1608Metric
PSRAM_R1: 100K; R_0603_1608Metric
PWR_FUSE1: Polyfuse; Fuse_1206_3216Metric_Pad1.42x1.75mm_HandSolder
PWR_PLUG1: Screw_Terminal_01x02; JST_SH_SM02B-SRSS-TB_1x02-1MP_P1.00mm_Horizontal
SPI_STORAG_C1: 100nF; C_0603_1608Metric
Sign-PbFree: LOGO_PBFREE
Sign-RecycleBin: LOGO_RECYCLEBIN_1
Sign-RoHS: LOGO_ROHS_1
TMPR1: 10K; R_0603_1608Metric
TP1, TP1#2: VIN; TestPoint_Pad_D1.0mm
TP2, TP2#2: VOut; TestPoint_Pad_D1.0mm
TP3, TP3#2: GND; TestPoint_Pad_D1.0mm
U1: MCP1525-TT; SOT-23
U2: ATSHA204A-MAHDA-T; ATSHA204A Auth SOIC8
U3: Battery_charger_CN3065_QFN8; QFN8 3.1x2.9mm QFNn-8 3x3 SON80P400X400X100-9N
U4: AHT20; AHT20 HT Sensor PSON100P300X300X110-6N
U6: TEMT6000; TEMT6000-SEN
USB_PLUG_R1, USB_PLUG_R3: 5k1; R_0603_1608Metric
USB_PLYG_R2: 150K; R_0603_1608Metric
VOLTAGE_REF_C1, VOLTAGE_REF_C2: 100nF; C_0603_1608Metric

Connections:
3V3: ATH20_C1.2, ATSHA_C1.2, AUR_C1.1, AUR_R1.1, AUR_l1.1, ESP32S1.20 (VDD3P3_RTC), ESP32S1.46 (VDD3P3_CPU), ESP32S1.55 (VDDA), ESP32S1.56 (VDDA), ESP_FLASH2.3 (IO2), ESP_FLASH2.7 (IO3), ESP_FLASH2.8 (VCC), ESP_FLASH3.3 (IO2), ESP_FLASH3.7 (IO3), ESP_FLASH3.8 (VCC), E_DTR_R1.1, E_RTS_R1.1, E_VDDA_C1.2, E_VDDA_C2.2, E_VDD_3_C1.1, E_VDD_3_C2.1, E_VDD_3_C3.1, E_VDD_CPU_C1.1, E_VDD_L1.1, E_VDD_RTC_C1.1, HX1.5 (VIN), HX_C3.2, I2C_SCL_R1.1, I2C_SDA_R1.2, IMR1.1, IMR2.1, IMU1.5 (VDDIO), IMU1.8 (VDD), IMU_C1.2, JICSP1.1, LCD1.4, LED1.4 (K), SPI_STORAG_C1.2, TP2.1, TP2#2.1, U2.8 (VCC), U4.2 (VDD), U6.COLLECTOR
3V3_PLUG: DIPSW1.3, DIPSW1.5, DIPSW1.7, DIPSW1.9, DIP_R1.2, ExtSW1.3, HX1.1 (VOUT), HX_C1.1, I2C_PLUG1.2, U1.1 (Vin), VOLTAGE_REF_C1.2
ADC_IN_IO04: DIPSW1.2, DIP_R2.1, DIP_R3.1, DIP_R4.1, DIP_R5.1, ESP32S1.11 (GPIO6/ADC1_CH5), ExtSW1.1
BAT_SENSE_IO21: BAT_SENSE_R1.1, BAT_SENSE_R2.2, ESP32S1.6 (GPIO1/ADC1_CH0)
CHIP_EN: ESP32S1.4 (CHIP_PU/RESET), E_RTS_C1.2, E_RTS_R1.2, JICSP1.7
DAC_CALIBRATION: ESP32S1.19 (GPIO14/ADC2_CH3), ESP32S1.24 (GPIO18/ADC2_CH7/DAC_1)
ESP_GPIO0_BOOT-DTR: ESP32S1.5 (GPIO0/BOOT), ESP32S1.52 (GPIO46), E_DTR_R1.2, JICSP1.6
FSPICLK_IO12: ESP32S1.17 (GPIO12/ADC2_CH1), ESP_FLASH2.6 (CLK), ESP_FLASH3.6 (CLK)
GND: ATH20_C1.1, ATSHA_C1.1, AUR1.2 (GND), AUR1.7 (GND), AUR_C1.2, AUR_C2.2, AUR_R2.2, BAT_SENSE_R1.2, CN3065_C2.1, CN3065_R1.1, CN3965_C1.1, DMP1045_R1.2, EPS1.4 (VSS), ESP32S1.8 (GPIO3/ADC1_CH2), ESP32S1.51 (GPIO45), ESP32S1.57 (GND), ESP32_SHIELD1.1 (Shield), ESP_FLASH1.4 (GND), ESP_FLASH1.9 (GND), ESP_FLASH2.4 (GND), ESP_FLASH3.4 (GND), E_LNA_ANT2.1 (GND), E_LNA_ANT2.2 (GND), E_LNA_C1.2, E_LNA_C2.2, E_RTS_C1.1, E_SPI_C1.2, E_SPI_C2.2, E_VDDA_C1.1, E_VDDA_C2.1, E_VDD_3_C1.2, E_VDD_3_C2.2, E_VDD_3_C3.2, E_VDD_3_C4.2, E_VDD_CPU_C1.2, E_VDD_RTC_C1.2, E_XTAL32_1.2, E_XTAL32_1.4, E_XTAL32_C1.2, E_XTAL32_C2.2, E_XTAL40_1.2, E_XTAL40_1.4, E_XTAL40_C1.2, E_XTAL40_C2.2, ExtSW1.2, ExtSWBAT_PLUG2.3, HX1.2 (GND), HX_C1.2, HX_C3.1, I2C_PLUG1.1, IMU1.6 (GND), IMU1.7 (GND), IMU_C1.1, J1.B1, J1.B12 (A12), JICSP1.2, LCD1.1, LCD1.2, LCD1.5, LCD1.6, LCD1.12, PWR_PLUG1.1, SPI_STORAG_C1.1, TMPR1.1, TP3.1, TP3#2.1, U1.3 (Vss), U2.4 (GND), U3.1 (V_Temp), U3.3 (GND), U3.9 (GND), U4.5 (GND), USB_PLUG_R1.2, USB_PLUG_R3.2, USB_PLYG_R2.2, VOLTAGE_REF_C1.1, VOLTAGE_REF_C2.1
GPIO8_I2C_SDA: ESP32S1.13 (GPIO8/ADC1_CH7), I2C_PLUG1.4, I2C_SDA_R1.1, IMR1.2, IMU1.14 (SDA), LCD1.10, U2.5 (SDA), U4.4 (SDA)
GPIO9_I2C_SCL: ESP32S1.14 (GPIO9/ADC1_CH8), I2C_PLUG1.3, I2C_SCL_R1.2, IMR2.2, IMU1.13 (SCL), LCD1.9, U2.6 (SCL), U4.3 (SCL)
IMU_CS_IO21: ESP32S1.27 (GPIO21), IMU1.12 (CS)
LCD2_CS_IO37: ESP32S1.42 (GPIO37), LCD1.8
LCD2_DC_IO36: ESP32S1.41 (GPIO36), LCD1.7
LCD2_LED_IO35: ESP32S1.40 (GPIO35), LCD1.3
LCD2_RST_IO38: ESP32S1.43 (GPIO38), LCD1.11
LED_B_IO05: ESP32S1.10 (GPIO5/ADC1_CH4), LED1.2 (BA)
LED_G_IO02: ESP32S1.7 (GPIO2/ADC1_CH1), LED1.1 (GA)
LED_R_IO04: ESP32S1.9 (GPIO4/ADC1_CH3), LR1.1
unnamed: AUR1.1 (FB), AUR_R1.2, AUR_R2.1
unnamed: AUR1.3 (SW), AUR_l1.2
unnamed: DIPSW1.1, DIP_R1.1
unnamed: DIPSW1.4, DIP_R2.2
unnamed: DIPSW1.6, DIP_R3.2
unnamed: DIPSW1.8, DIP_R4.2
unnamed: DIPSW1.10, DIP_R5.2
unnamed: ESP32S1.21 (GPIO15/ADC2_CH4/XTAL_32K_P), E_XTAL32_1.3, E_XTAL32_C1.1
unnamed: ESP32S1.22 (GPIO16/ADC2_CH5/XTAL_32K_N), E_XTAL32_1.1, E_XTAL32_C2.1
unnamed: ESP32S1.1 (LNA_IN/RF), E_LNA_C2.1, E_LNA_l1.2
unnamed: ESP32S1.49 (U0TXD/PROG/GPIO43), E_UART_TX_1.2
unnamed: ESP32S1.2 (VDD3P3), ESP32S1.3 (VDD3P3), E_VDD_3_C4.1, E_VDD_L1.2
unnamed: ESP32S1.53 (XTAL_N), E_XTAL40_1.3, E_XTAL40_C2.1
unnamed: ESP32S1.54 (XTAL_P), E_XTAL40_1.1, E_XTAL40_C1.1
unnamed: E_LNA_ANT1.1, E_LNA_ANT2.3 (SIG), E_LNA_C1.1, E_LNA_l1.1
unnamed: HX1.6 (C+), HX_C2.1
unnamed: HX1.4 (C-), HX_C2.2
unnamed: J1.A5 (CC1), USB_PLUG_R3.1
unnamed: J1.B5 (CC2), USB_PLUG_R1.1
unnamed: J1.S1 (SHIELD), USB_PLYG_R2.1
unnamed: LED1.3 (RA), LR1.2
unnamed: CN3065_R1.2, U3.2 (I_SET)
PLUG_PWR_3V3_EN_IO38: ESP32S1.39 (GPIO34), HX1.3 (EN)
RXD0: ESP32S1.50 (U0RXD/PROG/GPIO44), JICSP1.5
SPICLK: EPS1.6 (SCLK), ESP32S1.33 (SPICLK/GPIO30), ESP_FLASH1.6 (CLK)
SPICS0: ESP32S1.32 (SPICS0/GPIO29), ESP_FLASH1.1 (~CS)
SPICS1: EPS1.1 (~CE), ESP32S1.28 (SPI_CS1/GPIO26), PSRAM_R1.1
SPID: EPS1.5 (SiO0), ESP32S1.35 (SPID/GPIO32), ESP_FLASH1.5 (DI(IO0))
SPIHD: EPS1.7 (SIO3), ESP32S1.30 (SPIHD/GPIO27), ESP_FLASH1.7 (IO3)
SPIQ: EPS1.2 (SIO1), ESP32S1.34 (SPIQ/GPIO31), ESP_FLASH1.2 (DO(IO1))
SPIWP: EPS1.3 (SIO2), ESP32S1.31 (SPIWP/GPIO28), ESP_FLASH1.3 (IO2)
STDBY_LED_G: CN3065_STDBY_LED1.1 (K), U3.6 (LED_DONE)
STORAGE_2_CS_IO17: ESP32S1.23 (GPIO17/ADC2_CH6/DAC_2), ESP_FLASH2.1 (~CS)
STORAGE_CS_IO10: ESP32S1.15 (GPIO10/ADC1_CH9), ESP_FLASH3.1 (~CS)
STORAGE_MISO_SPIQ_IO13: ESP32S1.18 (GPIO13/ADC2_CH2), ESP_FLASH2.2 (DO(IO1)), ESP_FLASH3.2 (DO(IO1))
STORAGE_MOSI_SPID_IO11: ESP32S1.16 (GPIO11/ADC2_CH0), ESP_FLASH2.5 (DI(IO0)), ESP_FLASH3.5 (DI(IO0))
TEMT6000_IO33: ESP32S1.38 (GPIO33), TMPR1.2, U6.EMITTER
TXD0: E_UART_TX_1.1, JICSP1.4
USB_5V0: CN3065_STDBY_LED1.2 (A), CN3965_C1.2, DMP1045U_1.1, DMP1045_R1.1, DMP1045_SCHOT1.2 (A), PWR_FUSE1.1, U3.4 (VIN)
USB_5V0F: J1.A9, J1.B4, PWR_FUSE1.2, PWR_PLUG1.2
USB_D+: ESP32S1.26 (GPIO20/USB_D+/ADC2_CH9), J1.A6 (DP1), J1.B6 (DP2)
USB_D-: ESP32S1.25 (GPIO19/USB_D-/ADC2_CH8), J1.A7 (DN1), J1.B7 (DN2)
VDD_SPI: EPS1.8 (VCC), ESP32S1.29 (VDD_SPI), ESP_FLASH1.8 (VCC), E_SPI_C1.1, E_SPI_C2.1, PSRAM_R1.2
VIN: AUR1.4 (VIN_SW), AUR1.5 (VIN_A), AUR1.6 (EN), AUR_C2.1, DMP1045U_1.2, DMP1045_SCHOT1.1 (K), TP1.1, TP1#2.1
VIN_BAT: BAT_FUSE1.1, BAT_SENSE_R2.1, CN3065_C2.2, DMP1045U_1.3, U3.5 (BAT+), U3.8 (FB)
VIN_BATF: BAT_FUSE1.2, ExtSWBAT_PLUG2.1
VOLTAGE_REF_IO07: ESP32S1.12 (GPIO7/ADC1_CH6), U1.2 (Vout), VOLTAGE_REF_C2.2

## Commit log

2023-02-14 init commit

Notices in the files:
KiCad/LDAD_ATOM _PRO _LCD _ABS_Enclosure_52x48.kicad_pcb:
Copyright CC 2023
